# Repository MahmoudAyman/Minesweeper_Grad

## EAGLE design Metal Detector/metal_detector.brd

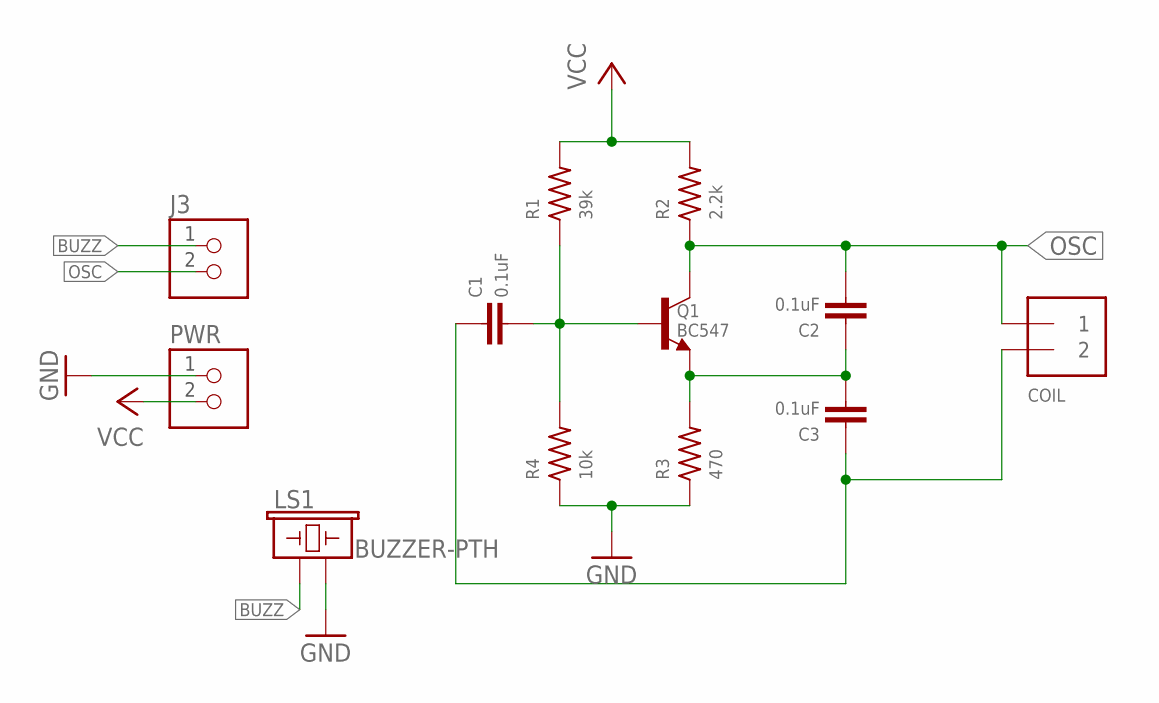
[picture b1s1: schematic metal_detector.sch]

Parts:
C1, C2, C3: 0.1uF; CAP-PTH-SMALL-KIT
COIL: TERMBLOCK_1X2; TERMBLOCK_1X2-3.5MM
J3: TERM-1X02-ADAFRUIT; 3.5MMTERM
LS1: BUZZER-PTH; BUZZER-12MM
PWR: TERM-1X02-ADAFRUIT; 3.5MMTERM
Q1: BC547; TO92
R1: 39k; 0207/10
R2: 2.2k; 0207/10
R3: 470; 0207/10
R4: 10k; 0207/10

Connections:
BUZZ: J3.1, LS1.+ (1)
GND: LS1.- (2), PWR.1, R3.1, R4.1
unnamed: C1.1, C3.1, COIL.2
unnamed: C2.1, C3.2, Q1.1 (E), R3.2
unnamed: C1.2, Q1.2 (B), R1.1, R4.2
OSC: C2.2, COIL.1, J3.2, Q1.3 (C), R2.1
VCC: PWR.2, R1.2, R2.2

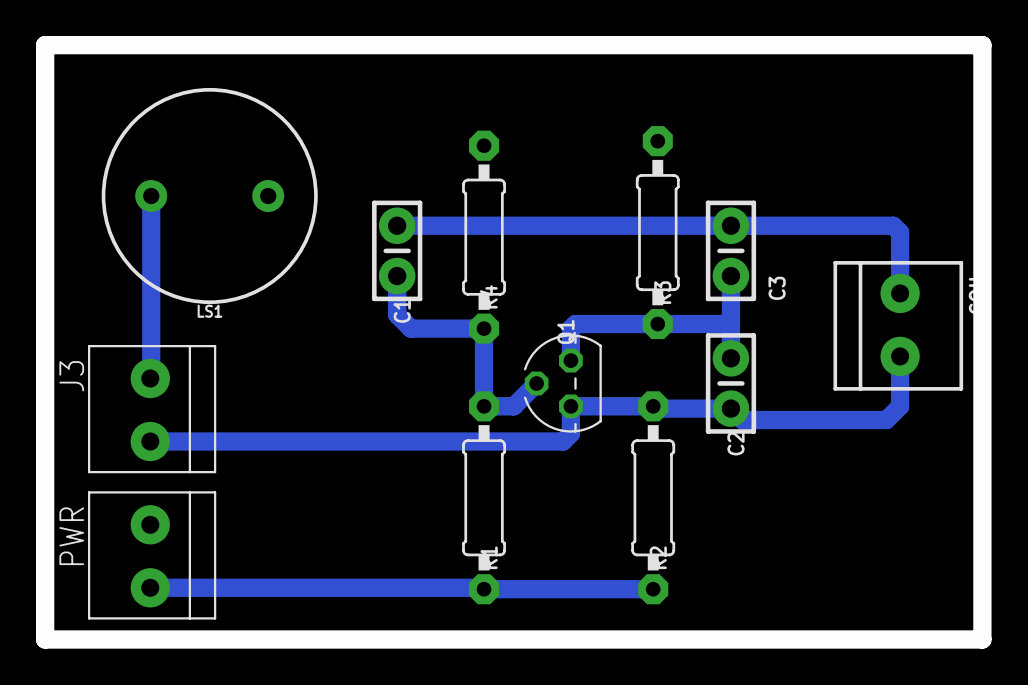
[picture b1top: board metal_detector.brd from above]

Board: 2 copper layers, 52.1 x 33.0 mm, 12 parts (0 on the bottom side), 7 nets.

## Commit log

2019-05-13 added the test code for the line follower
2019-05-13 Added the basic library for the motor driver
2019-05-14 added the code for the motor contorl via bluetooth
2019-06-15 added the code for the metal detector
2019-06-15 added the PCB design for the metal detector
2019-06-28 added the integrated code and the processing mapping code
2019-06-29 added the required libraries

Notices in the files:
parts and their libraries:
microbuilder: This work is placed in the public domain, and may be freely used for commercial and non-commercial work with the following conditions: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
SparkFun-Capacitors: Licensing: Creative Commons ShareAlike 4.0 International - https://creativecommons.org/licenses/by-sa/4.0
